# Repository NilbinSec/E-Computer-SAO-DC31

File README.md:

# E-Computer-SAO-DC31

This is the DEFCON E-Computer SAO Repository for DEFCON 31. We hope you enjoy the SAO thank you for supporting NilbinSec as we continue to grow.

## BOM:
1x Shrouded 2x3 Pin SAO adapter

1x 100ohm THT resistor (PN# CF14JT100R) (https://www.digikey.com/en/products/detail/stackpole-electronics-inc/CF14JT100R/1741261)

1x Blue THT LED (PN#VAOL-5701SBY4) (https://www.mouser.com/ProductDetail/VCC/VAOL-5701SBY4?qs=io7aH2hdVh6rMvoRumIRlg%3D%3D&countryCode=US&currencyCode=USD)

2x White Sideview SMD LED (PN#743-IN-S126ASUW) (https://www.mouser.com/ProductDetail/Inolux/IN-S126ASUW?qs=fAHHVMwC%252BbgCuuXulbNrlg%3D%3D&countryCode=US&currencyCode=USD)

Special Thanks to 2PAC and Anxious Analyst for their efforts designing and developing this year's SAO!

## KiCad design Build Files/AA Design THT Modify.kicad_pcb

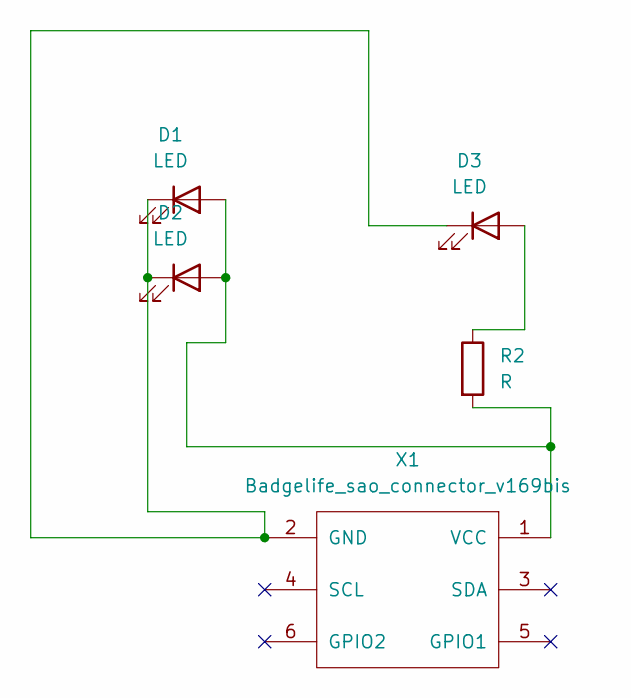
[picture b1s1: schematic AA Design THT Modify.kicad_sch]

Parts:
D1, D2: LED; LED_1206_3216Metric_Pad1.42x1.75mm_HandSolder
D3: LED; LED_D5.0mm_IRGrey
R2: R; R_Axial_DIN0204_L3.6mm_D1.6mm_P5.08mm_Vertical
X1: Badgelife_sao_connector_v169bis; Badgelife-SAOv169-SAO-2x3

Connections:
unnamed: D1.2 (A), D2.2 (A), R2.2, X1.1 (VCC)
unnamed: D1.1 (K), D2.1 (K), D3.1 (K), X1.2 (GND)
unnamed: D3.2 (A), R2.1

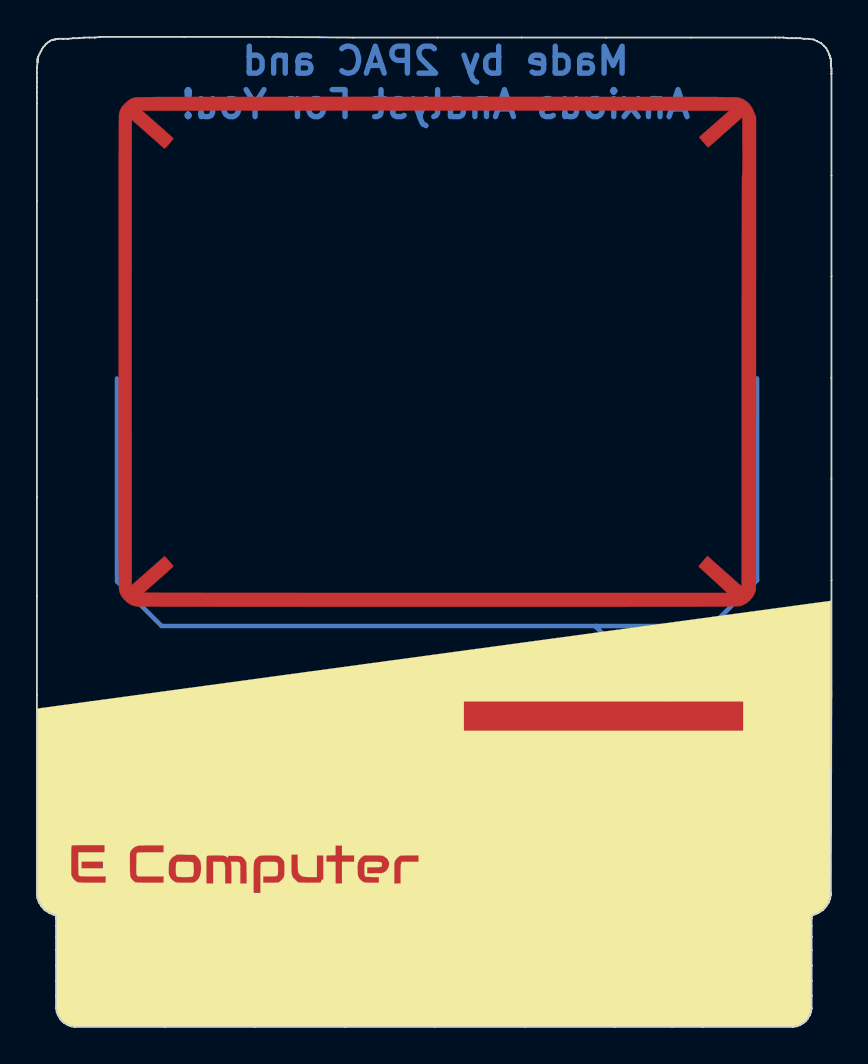
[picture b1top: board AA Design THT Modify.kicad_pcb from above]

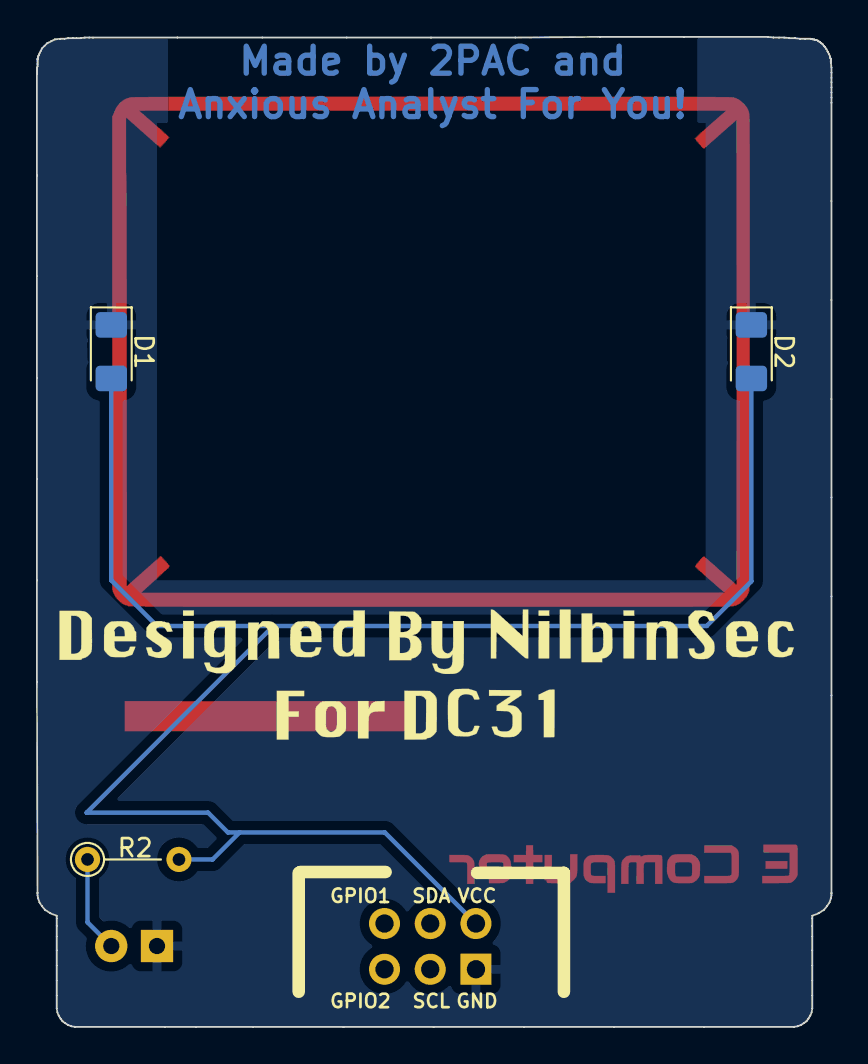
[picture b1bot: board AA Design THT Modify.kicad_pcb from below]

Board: 2 copper layers, 44.1 x 55.0 mm, 5 parts (3 on the bottom side), 3 nets.
